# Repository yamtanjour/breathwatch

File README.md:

# BreathWatch – Portable Air Quality Monitor

*Prototype using breadboard*

Personal IoT device using STM32 to monitor indoor air quality and send data to a Flutter mobile app via Bluetooth.

## Hardware (PCB Design)

*3D view of PCB*

*PCB layout*

## Circuit Overview

*Detailed connections*

*PCB schematic*

## Features

- **Sensors:** ENS160 (eCO2 / TVOC / air quality index) + AHT21 (temperature & humidity) over I2C
- **Bluetooth UART bridge** to Flutter companion app
- **Push button & status LED** control via MOSFET

## Hardware
- STM32F401 microcontroller dev board
- ENS160 air quality sensor
- AHT21 temperature & humidity sensor
- PCB

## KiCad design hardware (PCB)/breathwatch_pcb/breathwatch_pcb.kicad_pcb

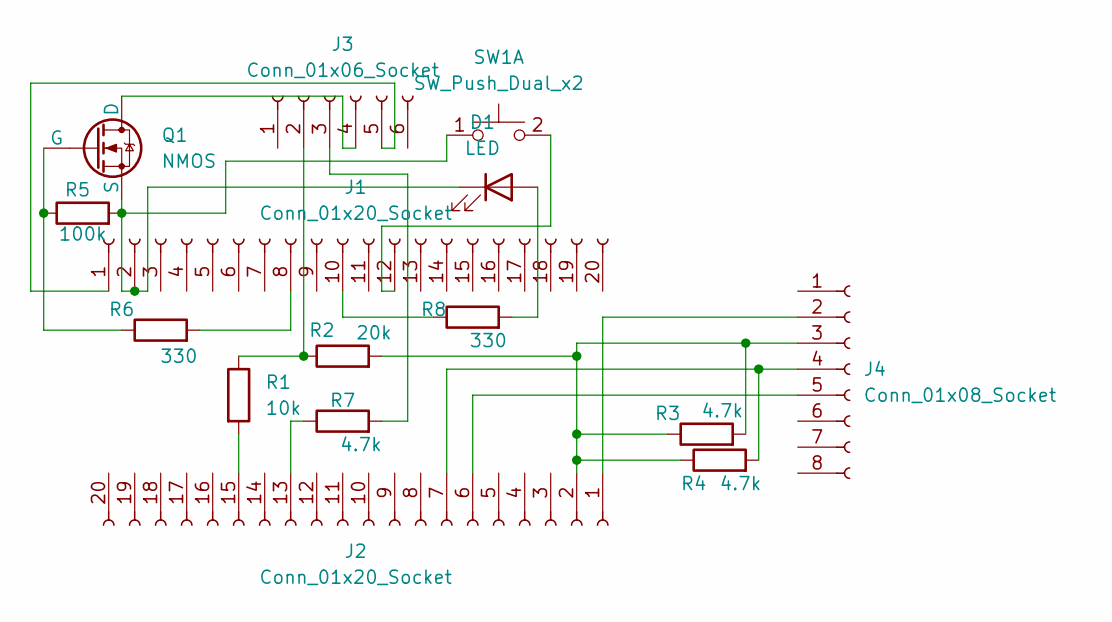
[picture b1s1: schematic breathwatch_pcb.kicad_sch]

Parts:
D1: LED; LED_D5.0mm
J1, J2: Conn_01x20_Socket; PinSocket_1x20_P2.54mm_Vertical
J3: Conn_01x06_Socket; PinSocket_1x06_P2.54mm_Vertical
J4: Conn_01x08_Socket; PinSocket_1x08_P2.54mm_Vertical
Q1: NMOS; TO-220-3_Vertical
R1: 10k; R_0815_2038Metric
R2: 20k; R_0815_2038Metric
R3, R4, R7: 4.7k; R_0815_2038Metric
R5: 100k; R_0815_2038Metric
R6, R8: 330; R_0815_2038Metric
SW1: SW_Push_Dual_x2; SW_PUSH_6mm_H4.3mm

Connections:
unnamed: D1.2 (A), R8.2
unnamed: D1.1 (K), J1.2, Q1.3 (S), R5.2, SW1.1 (C)
unnamed: J1.1, J3.5
unnamed: J1.8, R6.2
unnamed: J1.10, R8.1
unnamed: J1.12, SW1.2 (D)
unnamed: J2.1, J4.2
unnamed: J2.2, J4.3, R2.2, R3.1, R3.2, R4.1
unnamed: J2.6, J4.5
unnamed: J2.7, J4.4, R4.2
unnamed: J2.13, R7.1
unnamed: J2.15, R1.2
unnamed: J3.2, R1.1, R2.1
unnamed: J3.3, R7.2
unnamed: J3.4, Q1.1 (D)
unnamed: Q1.2 (G), R5.1, R6.1

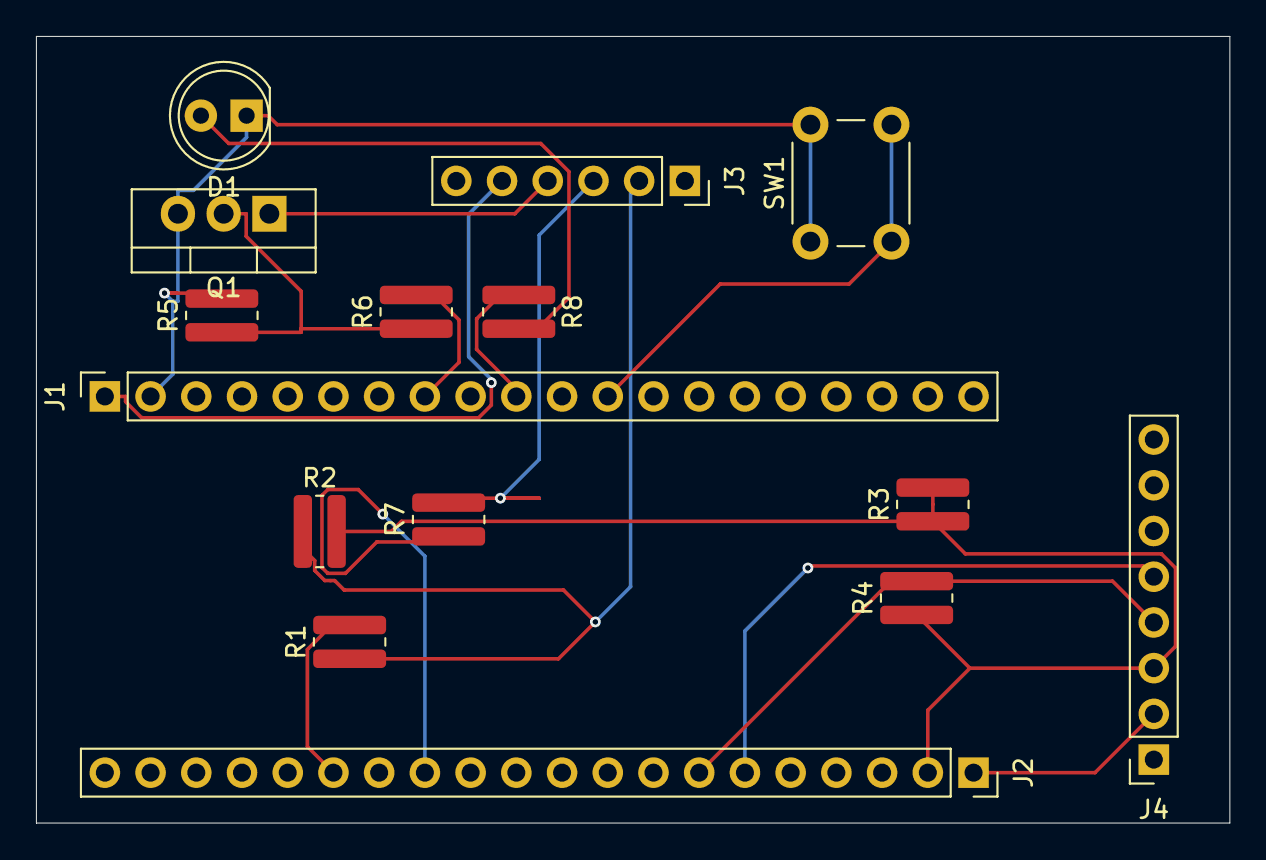
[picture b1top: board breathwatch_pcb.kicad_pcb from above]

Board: 2 copper layers, 66.3 x 43.7 mm, 15 parts (0 on the bottom side), 16 nets.

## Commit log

2026-01-18 created schematic
2026-01-18 pcb board set up
2026-01-18 added wiring
2026-01-18 added name
2026-01-21 fixed a few things (PCB, Schematic)
2026-01-24 Fixed a bit (PCB)
2026-01-24 fixed a bit, started code
2026-01-24 added button to PCB
2026-01-25 fixed routing
2026-01-25 fixed a bit
2026-01-25 changed a bit
2026-01-27 added a bit to code
2026-01-31 added sensor reading + writing, changed a bit (PCB)
2026-01-31 added bluetooth and started App
2026-02-21 changed from ESP32 to STM32
2026-02-21 added README
2026-02-22 PCB Design
2026-02-22 changed ReadME
